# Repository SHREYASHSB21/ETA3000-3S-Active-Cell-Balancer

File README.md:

\# ETA3000 3S Active Cell Balancer

A compact 3-cell (3S) inductive active cell-balancing module designed using the ETA3000 active cell-balancing IC.

!\[3D View](Images/3d\_view.png)

\## Project Overview

This project was developed as part of an Electronics Systems task to design and develop a compact active cell-balancing module for a 3S battery system intended for drone applications.

In conventional passive cell balancing, excess energy from a higher-voltage cell is dissipated as heat through a balancing resistor. This results in energy loss and additional thermal stress.

The ETA3000-based design uses \*\*inductive active cell balancing\*\*, where energy is transferred between cells instead of simply being dissipated as heat.

The target balancing current for this design is \*\*up to 1.2 A\*\*.

\---

\## Specifications

| Parameter                | Specification              |

| ------------------------ | -------------------------- |

| Battery configuration    | 3S                         |

| Number of cells          | 3                          |

| Balancing method         | Inductive active balancing |

| Balancing IC             | ETA3000                    |

| Target balancing current | Up to 1.2 A                |

| PCB design software      | KiCad                      |

| PCB type                 | Custom 2-layer PCB         |

| Main design objective    | Compact form factor        |

| Application              | Drone battery system       |

\---

\## Design Architecture

The three battery cells are connected to the active-balancing circuit through the cell input connections.

The ETA3000 controls the inductive energy-transfer process between the cells. When a voltage imbalance exists, energy can be transferred from a higher-voltage cell toward a lower-voltage cell.

Unlike passive balancing, the energy is not intentionally converted into heat through a large balancing resistor.

\### Basic concept

```text

&#x20;Higher-voltage cell

&#x20;       │

&#x20;       ▼

&#x20;  ETA3000 Control

&#x20;       │

&#x20;       ▼

&#x20;  Inductive Energy

&#x20;     Transfer

&#x20;       │

&#x20;       ▼

&#x20;Lower-voltage cell

```

The actual switching and energy-transfer behaviour is determined by the ETA3000 architecture and its external components.

\---

\## Schematic

!\[Schematic](Images/schematic.png)

The schematic was designed according to the ETA3000 datasheet/application information and the requirements of the 3S battery configuration.

Important design considerations include:

\* Correct cell connections

\* ETA3000 power connections

\* Inductive energy-transfer components

\* Local bypass/decoupling capacitors

\* Appropriate component voltage ratings

\* High-current balancing paths

\* Correct grounding and return paths

\---

\## PCB Layout

!\[PCB Layout](Images/pcb\_layout.png)

The PCB layout was designed with compactness as one of the primary objectives.

Since the intended application is a drone battery system, reducing PCB area and unnecessary wiring is important.

The layout therefore considers:

\* Short high-current paths

\* Compact placement of the balancing components

\* Inductor placement

\* Decoupling capacitor placement

\* Practical routing

\* Copper width for balancing-current paths

\* Component accessibility

\* Clearance between different electrical nodes

\---

\## Compact Layout Considerations

A major challenge of the project was fitting the complete balancing circuit into a small PCB area.

The placement was performed with the following priorities:

1\. Keep the main energy-transfer paths short.

2\. Keep relevant passive components close to the ETA3000.

3\. Minimize unnecessary routing.

4\. Maintain suitable electrical clearances.

5\. Provide sufficiently wide copper for higher-current paths.

6\. Keep the overall board compact.

The final PCB layout was then checked using KiCad's Design Rules Checker.

\---

\## Current Handling

The target balancing current is approximately:

\*\*1.2 A\*\*

PCB trace width cannot be selected only from the nominal current. The actual design should also consider:

\* Copper thickness

\* Trace width

\* Trace length

\* Allowable temperature rise

\* PCB layer

\* Ambient temperature

\* Current duty cycle

The higher-current balancing paths were therefore given greater consideration during PCB routing than low-current signal connections.

\### Trace-width calculation

The final trace width should be justified using a PCB trace-width calculation based on the actual copper thickness and acceptable temperature rise.

> Note: The numerical trace-width value should be added here based on the actual PCB copper thickness and the calculation used for this design.

\---

\## ETA3000 Custom Footprint

The ETA3000 footprint was not available directly in the default KiCad library used during the project.

A custom KiCad footprint was therefore created/imported for the ETA3000 package.

The custom footprint is included in:

```text

ETA3000D2I.pretty/

└── ETA3000D2I.kicad\_mod

```

The footprint dimensions should be verified against the manufacturer's package drawing before fabrication.

\---

\## Component Selection

Component selection was performed with consideration for:

\* ETA3000 recommended operating conditions

\* Voltage ratings

\* Current capability

\* Package size

\* PCB availability

\* Compact placement

\* Suitable footprints

For future fabrication, components should be checked against their latest manufacturer datasheets before ordering.

\---

\## PCB Manufacturing Files

The `Gerbers/` directory contains the generated manufacturing files for the PCB.

These files can be used to inspect or manufacture the PCB using a PCB fabrication service.

Typical manufacturing outputs include:

\* Front copper

\* Back copper

\* Solder masks

\* Silkscreens

\* Board outline

\* Drill files

\---

\## Repository Structure

```text

ETA3000-3S-Active-Cell-Balancer/

│

├── ACB\_BMS.kicad\_pro

├── ACB\_BMS.kicad\_sch

├── ACB\_BMS.kicad\_pcb

│

├── ETA3000D2I.pretty/

│   └── ETA3000D2I.kicad\_mod

│

├── Images/

│   ├── schematic.png

│   ├── pcb\_layout.png

│   └── 3d\_view.png

│

├── Gerbers/

│   └── PCB manufacturing files

│

├── .gitignore

└── README.md

```

\---

\## Tools Used

\* KiCad

\* ETA3000 datasheet

\* ETA3000 application/reference information

\* PCB Design Rules Checker

\* PCB trace-width calculations

\---

\## Project Status

\*\*PCB design completed.\*\*

The current repository contains the KiCad schematic, PCB layout, custom ETA3000 footprint and manufacturing outputs.

Further validation would include:

\* PCB fabrication

\* Component assembly

\* Power-up testing

\* Cell-voltage measurement

\* Balancing-current measurement

\* Thermal testing

\* Verification of balancing behaviour under different cell-voltage conditions

\---

\## Learning Outcomes

This project involved practical work in:

\* Reading an IC datasheet

\* Understanding active cell balancing

\* Inductive energy transfer

\* Component selection

\* Custom KiCad footprint handling

\* Schematic design

\* PCB placement

\* High-current PCB routing

\* PCB trace-width considerations

\* Design Rule Checking

\* Gerber generation

\* Git/GitHub version control

\---

\## Author

\*\*Shreyash Birdawade\*\*

Electronics \& Telecommunication Engineering

GitHub: \[@SHREYASHSB21](https://github.com/SHREYASHSB21)

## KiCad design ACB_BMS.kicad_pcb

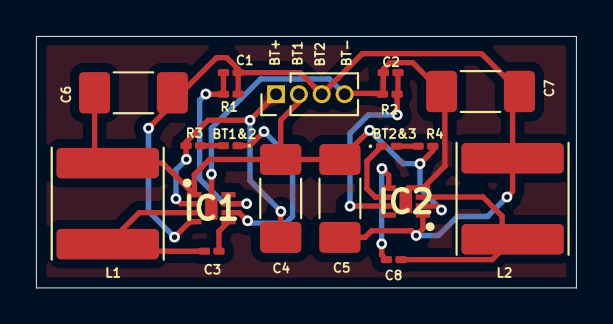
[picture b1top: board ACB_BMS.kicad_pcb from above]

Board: 2 copper layers, 30.0 x 14.0 mm, 19 parts (0 on the bottom side), 14 nets.

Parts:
BT1&2, BT2&3: LED; LED_0201_0603Metric_Pad0.64x0.40mm_HandSolder
C1, C2: 800pf; C_0201_0603Metric_Pad0.64x0.40mm_HandSolder
C3, C8: 10nf; C_0201_0603Metric_Pad0.64x0.40mm_HandSolder
C4, C5, C6, C7: 10uf; C_1808_4520Metric_Pad1.72x2.30mm_HandSolder
IC1, IC2: ETA3000D2I
J1: Conn_01x04_Pin; PinHeader_1x04_P1.27mm_Vertical
L1, L2: 0.8uH; L_Sunlord_SWPA6045S
R1, R2: 40k; R_0201_0603Metric_Pad0.64x0.40mm_HandSolder
R3, R4: R; R_0201_0603Metric_Pad0.64x0.40mm_HandSolder

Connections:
GND: C2.2, C7.1, IC1.9 (EP), IC2.4 (BATN), IC2.9 (EP), J1.4, R2.2
unnamed: BT1&2.2 (A), R3.1
unnamed: BT1&2.1 (K), IC1.6 (STAT)
unnamed: BT2&3.2 (A), R4.1
unnamed: BT2&3.1 (K), IC2.6 (STAT)
unnamed: C4.1, C5.2, C6.2, IC1.1 (BATC), IC2.2 (BATP), J1.2, L1.2, R4.2
unnamed: C1.2, C5.1, C6.1, C7.2, IC1.4 (BATN), IC2.1 (BATC), J1.3, L2.2, R1.2
unnamed: C4.2, IC1.2 (BATP), J1.1, R3.2
unnamed: C3.1, IC1.5 (BIAS)
unnamed: C1.1, IC1.7 (ISET), R1.1
unnamed: C3.2, IC1.3 (SW), L1.1
unnamed: C8.1, IC2.5 (BIAS)
unnamed: C2.1, IC2.7 (ISET), R2.1
unnamed: C8.2, IC2.3 (SW), L2.1
